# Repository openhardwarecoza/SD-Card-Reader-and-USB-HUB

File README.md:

# SD-Card-Reader-and-USB-HUB
Single PCB for FE1.1 USB Hub and GL827 SD Card Readers x4

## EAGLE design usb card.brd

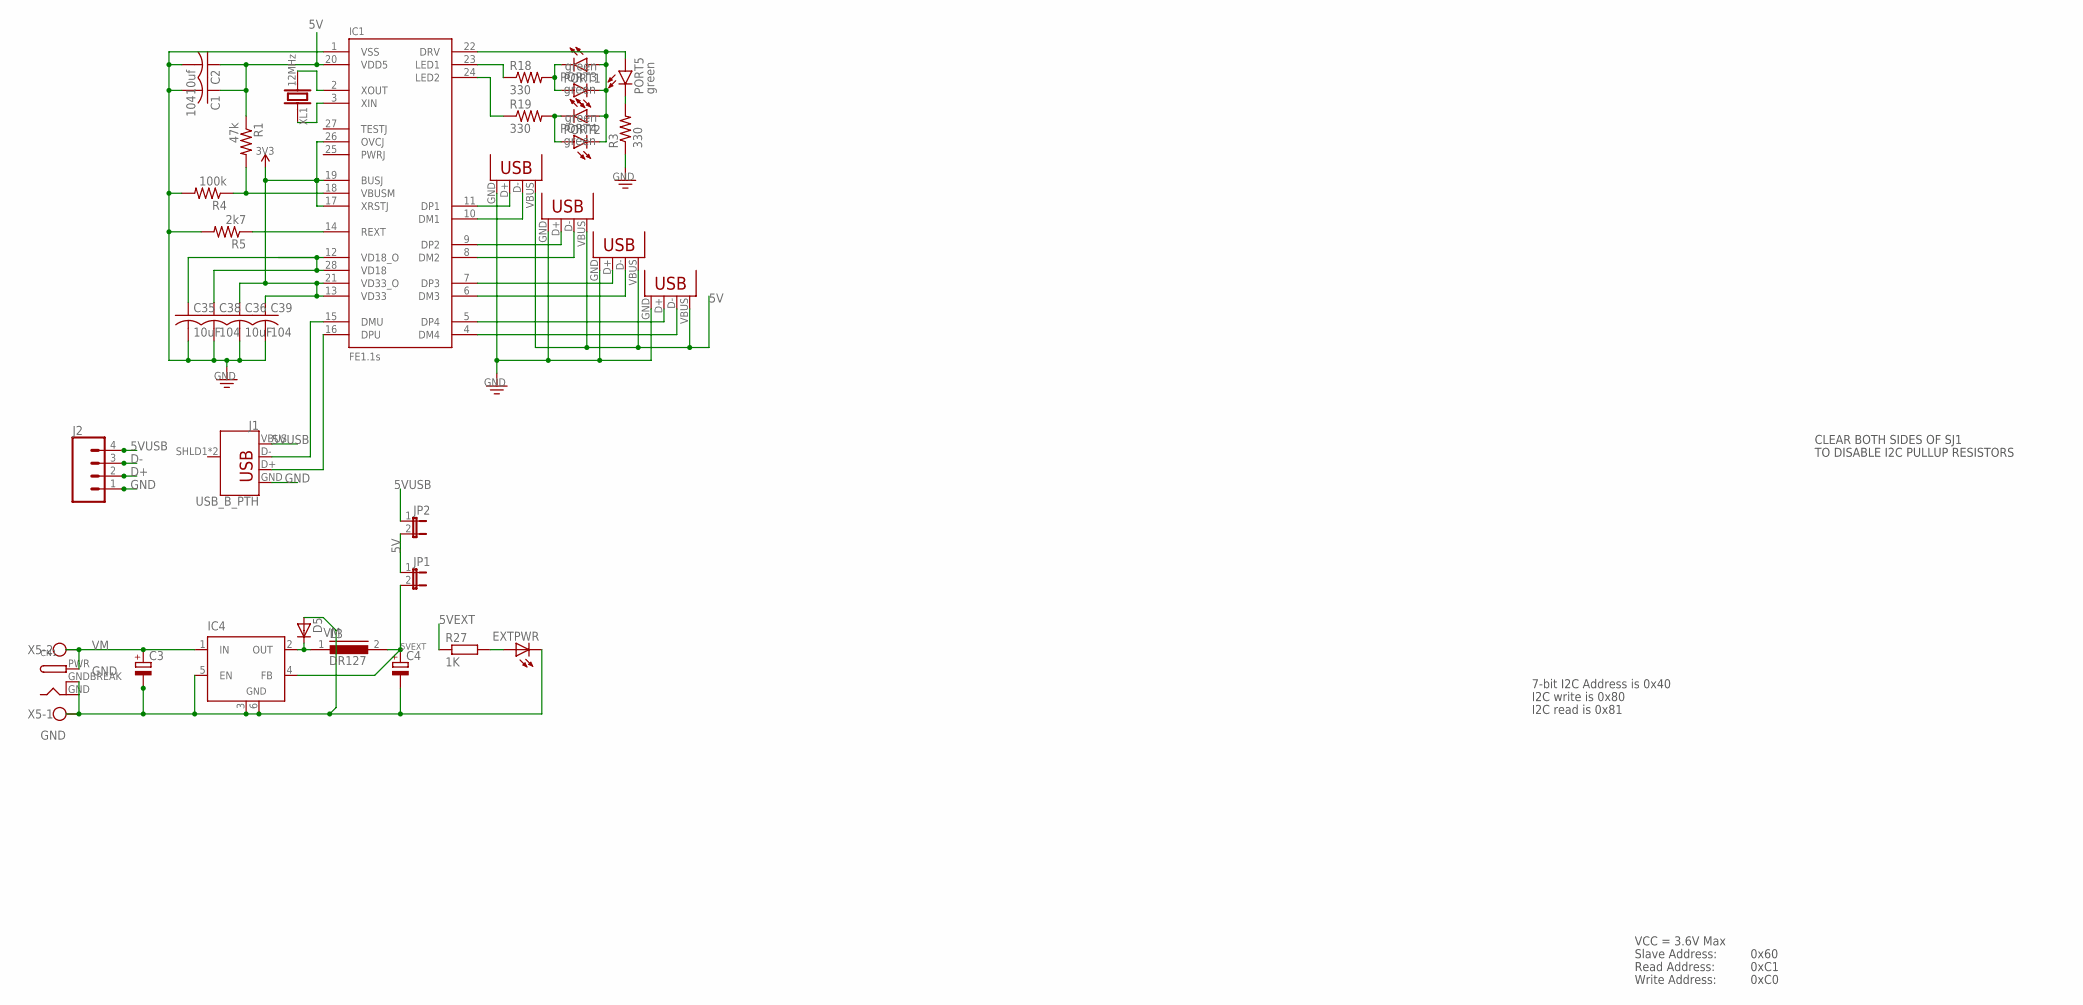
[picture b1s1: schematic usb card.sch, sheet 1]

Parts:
C1, C38, C39: 104; C1206
C2: 10uf; C1206
C3, C4: CPOL-EUE3.5-8; E3,5-8
C35, C36: 10uF; C1206
CN1: DCBARRELPTH; DCJACK_2MM_PTH
D5: D-SOD-80; SOD80
EXTPWR: LEDCHIPLED_1206; CHIPLED_1206
IC1: FE1.1S; FE1.1S_SSOP-28
IC4: LM2596S; TO263-5
J1: USB_B_PTH; USB-B-PTH
J2: CONN_04; 1X04
JP1, JP2: JP1E; JP1
L3: DR127
PORT1, PORT2, PORT3, PORT4, PORT5: green; LED-1206
R1: 47k; R1206
R3, R18, R19: 330; R1206
R4: 100k; R1206
R5: 2k7; R1206
R27: 1K; M1206
USB2, USB3, USB4, USB5: USBA-PTH; USB-A-F-PTH
X5: W237-102
XL1: 12MHz; HC49S

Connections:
3V3: C36.1, C39.1, IC1.13 (VD33), IC1.17 (XRSTJ), IC1.19 (BUSJ), IC1.21 (VD33_O), IC1.26 (OVCJ)
5V: C1.1, C2.1, IC1.20 (VDD5), JP1.1, JP2.2, R1.1, USB2.VBUS, USB3.VBUS, USB4.VBUS, USB5.VBUS; also elsewhere on the board
5VEXT: C4.+, IC4.4 (FB), JP1.2, L3.2, R27.1
5VUSB: J1.VBUS, J2.4, JP2.1
D+: IC1.16 (DPU), J1.D+, J2.2
D-: IC1.15 (DMU), J1.D-, J2.3
DM1: IC1.10 (DM1), USB5.D-; also elsewhere on the board
DM2: IC1.8 (DM2), USB4.D-; also elsewhere on the board
DM3: IC1.6 (DM3), USB3.D-; also elsewhere on the board
DM4: IC1.4 (DM4), USB2.D-; also elsewhere on the board
DP1: IC1.11 (DP1), USB5.D+; also elsewhere on the board
DP2: IC1.9 (DP2), USB4.D+; also elsewhere on the board
DP3: IC1.7 (DP3), USB3.D+; also elsewhere on the board
DP4: IC1.5 (DP4), USB2.D+; also elsewhere on the board
GND: C1.2, C2.2, C3.-, C4.-, C35.2, C36.2, C38.2, C39.2, CN1.GND, CN1.GNDBREAK, D5.2 (A), EXTPWR.C, IC1.1 (VSS), IC4.3 (GND), IC4.5 (EN), IC4.6 (GND), J1.GND, J2.1, R3.1, R4.2, R5.2, USB2.GND, USB3.GND, USB4.GND, USB5.GND, X5.1; also elsewhere on the board
unnamed: IC1.14 (REXT), R5.1
unnamed: PORT2.C, PORT4.A, R19.2
unnamed: IC1.2 (XOUT), XL1.2
unnamed: C35.1, C38.1, IC1.12 (VD18_O), IC1.28 (VD18)
unnamed: IC1.3 (XIN), XL1.1
unnamed: IC1.18 (VBUSM), R1.2, R4.1
unnamed: PORT1.C, PORT3.A, R18.2
unnamed: PORT5.C, R3.2
unnamed: IC1.23 (LED1), R18.1
unnamed: IC1.24 (LED2), R19.1
unnamed: IC1.22 (DRV), PORT1.A, PORT2.A, PORT3.C, PORT4.C, PORT5.A
unnamed: D5.1 (C), IC4.2 (OUT), L3.1
unnamed: EXTPWR.A, R27.2
VM: C3.+, CN1.PWR, IC4.1 (IN), X5.2

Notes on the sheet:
CLEAR BOTH SIDES OF SJ1
TO DISABLE I2C PULLUP RESISTORS
7-bit I2C Address is 0x40
I2C write is 0x80
I2C read is 0x81
VCC = 3.6V Max
Read Address:
Write Address:
Slave Address:
0x60
0xC1
0xC0

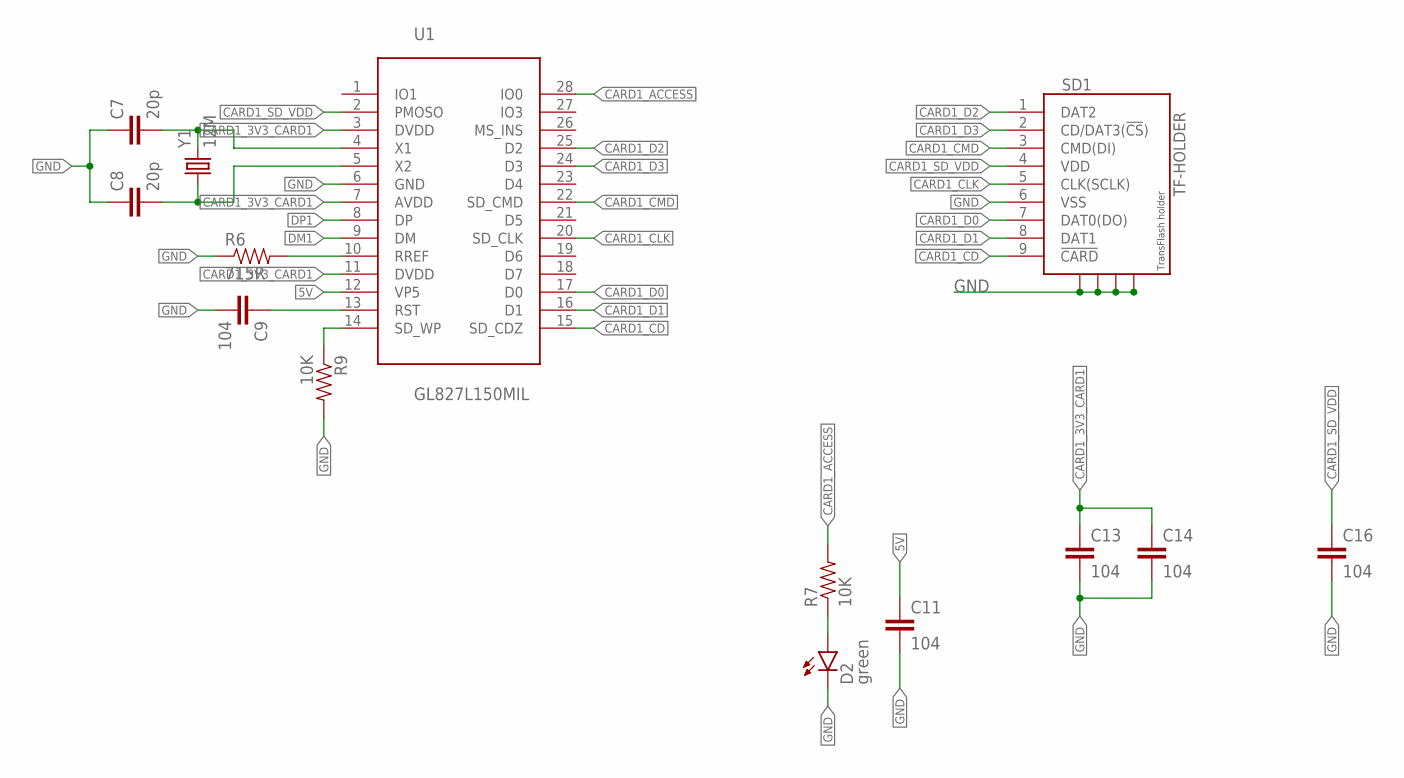
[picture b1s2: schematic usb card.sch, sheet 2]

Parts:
C7, C8: 20p; 1206
C9, C11, C13, C14, C16: 104; 1206
D2: green; LED-1206
R6: 715R; 1206
R7, R9: 10K; 1206
SD1: TF-HOLDER; TF-PULL
U1: GL827L150MIL; SSOP28-39
Y1: 12M; HC49US

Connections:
5V: C11.1, U1.12 (VP5); also elsewhere on the board
CARD1_3V3_CARD1: C13.1, C14.1, U1.3 (DVDD), U1.7 (AVDD), U1.11 (DVDD)
CARD1_ACCESS: R7.2, U1.28 (IO0)
CARD1_CD: SD1.9 (!CARD), U1.15 (SD_CDZ)
CARD1_CLK: SD1.5 (CLK(SCLK)), U1.20 (SD_CLK)
CARD1_CMD: SD1.3 (CMD(DI)), U1.22 (SD_CMD)
CARD1_D0: SD1.7 (DAT0(DO)), U1.17 (D0)
CARD1_D1: SD1.8 (DAT1), U1.16 (D1)
CARD1_D2: SD1.1 (DAT2), U1.25 (D2)
CARD1_D3: SD1.2 (CD/DAT3(!CS!)), U1.24 (D3)
CARD1_SD_VDD: C16.1, SD1.4 (VDD), U1.2 (PMOSO)
DM1: U1.9 (DM); also elsewhere on the board
DP1: U1.8 (DP); also elsewhere on the board
GND: C7.1, C8.1, C9.2, C11.2, C13.2, C14.2, C16.2, D2.C, R6.1, R9.2, SD1.6 (VSS), SD1.S1, SD1.S2, SD1.S3, SD1.S4, U1.6 (GND); also elsewhere on the board
unnamed: C7.2, U1.4 (X1), Y1.2
unnamed: C8.2, U1.5 (X2), Y1.1
unnamed: R6.2, U1.10 (RREF)
unnamed: C9.1, U1.13 (RST)
unnamed: D2.A, R7.1
unnamed: R9.1, U1.14 (SD_WP)

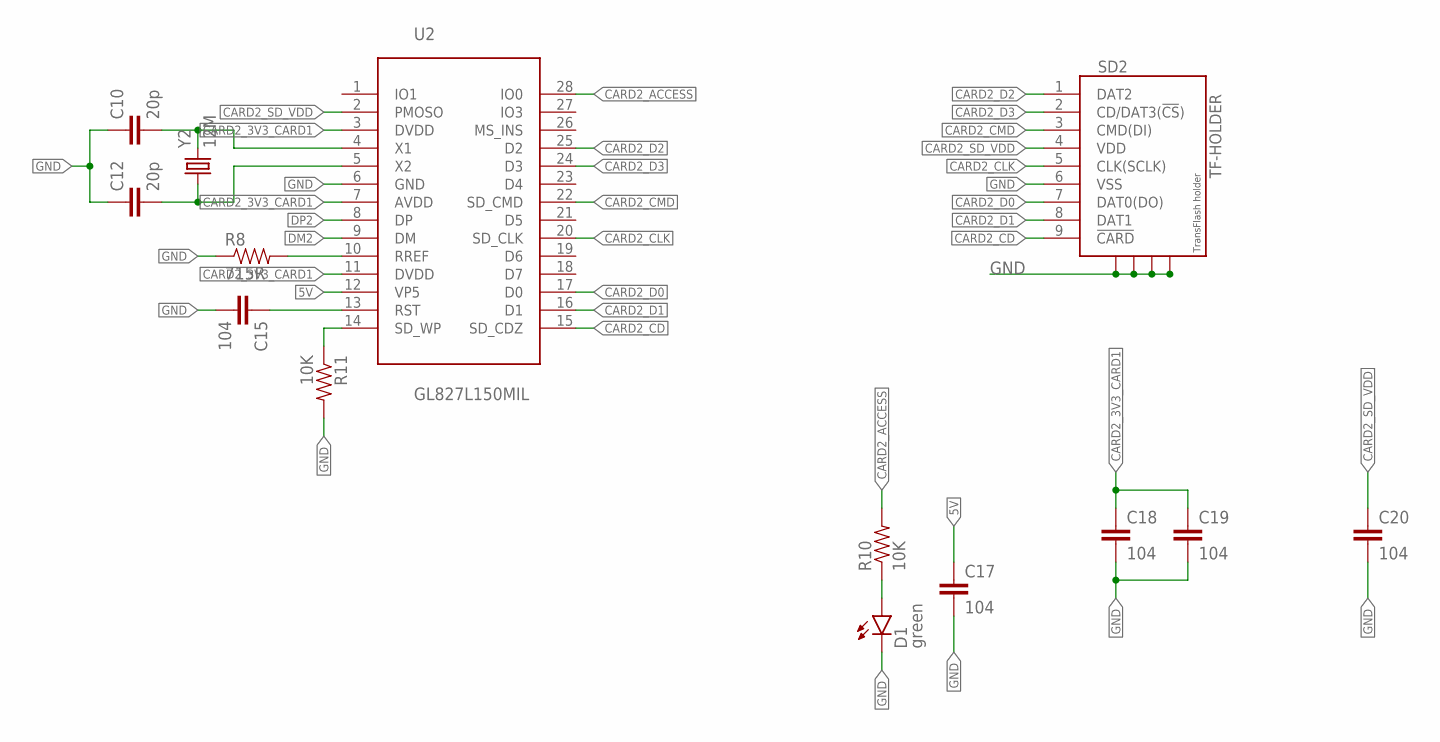
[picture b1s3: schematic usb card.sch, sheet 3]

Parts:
C10, C12: 20p; 1206
C15, C17, C18, C19, C20: 104; 1206
D1: green; LED-1206
R8: 715R; 1206
R10, R11: 10K; 1206
SD2: TF-HOLDER; TF-PULL
U2: GL827L150MIL; SSOP28-39
Y2: 12M; HC49US

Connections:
5V: C17.1, U2.12 (VP5); also elsewhere on the board
CARD2_3V3_CARD1: C18.1, C19.1, U2.3 (DVDD), U2.7 (AVDD), U2.11 (DVDD)
CARD2_ACCESS: R10.2, U2.28 (IO0)
CARD2_CD: SD2.9 (!CARD), U2.15 (SD_CDZ)
CARD2_CLK: SD2.5 (CLK(SCLK)), U2.20 (SD_CLK)
CARD2_CMD: SD2.3 (CMD(DI)), U2.22 (SD_CMD)
CARD2_D0: SD2.7 (DAT0(DO)), U2.17 (D0)
CARD2_D1: SD2.8 (DAT1), U2.16 (D1)
CARD2_D2: SD2.1 (DAT2), U2.25 (D2)
CARD2_D3: SD2.2 (CD/DAT3(!CS!)), U2.24 (D3)
CARD2_SD_VDD: C20.1, SD2.4 (VDD), U2.2 (PMOSO)
DM2: U2.9 (DM); also elsewhere on the board
DP2: U2.8 (DP); also elsewhere on the board
GND: C10.1, C12.1, C15.2, C17.2, C18.2, C19.2, C20.2, D1.C, R8.1, R11.2, SD2.6 (VSS), SD2.S1, SD2.S2, SD2.S3, SD2.S4, U2.6 (GND); also elsewhere on the board
unnamed: C10.2, U2.4 (X1), Y2.2
unnamed: C12.2, U2.5 (X2), Y2.1
unnamed: R8.2, U2.10 (RREF)
unnamed: C15.1, U2.13 (RST)
unnamed: D1.A, R10.1
unnamed: R11.1, U2.14 (SD_WP)

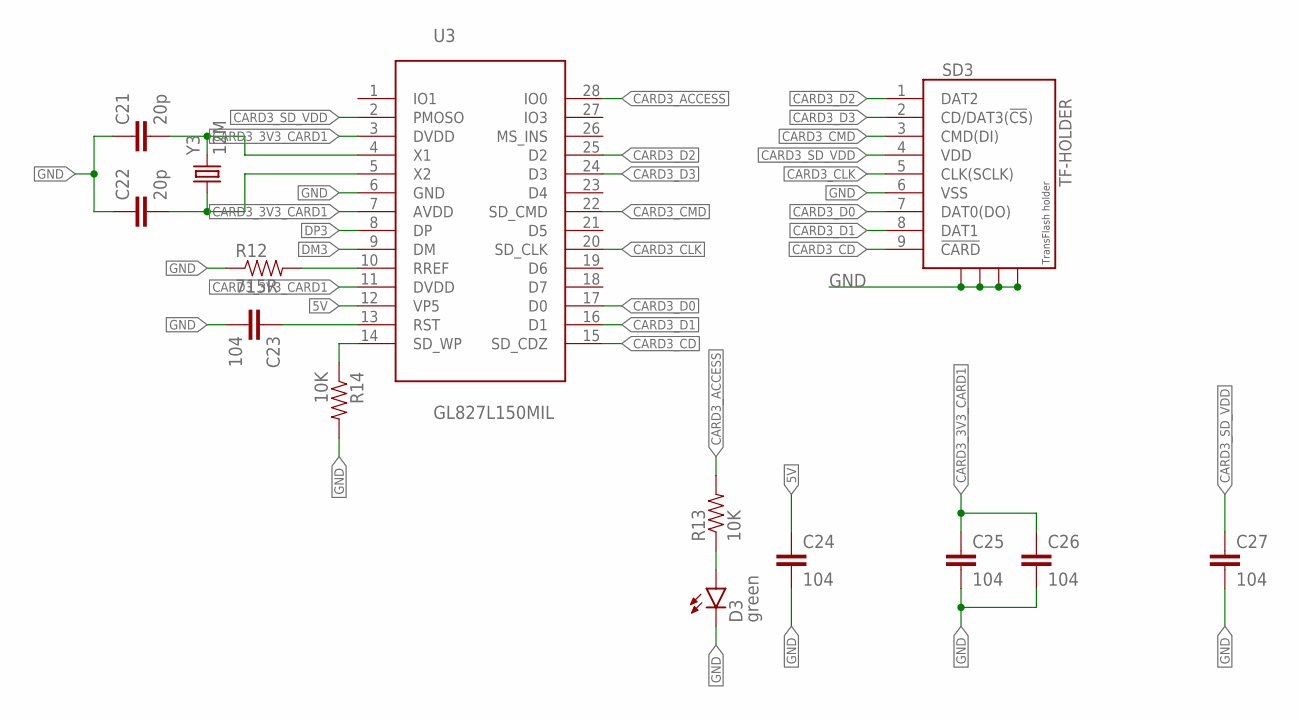
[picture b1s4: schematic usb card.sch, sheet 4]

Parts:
C21, C22: 20p; 1206
C23, C24, C25, C26, C27: 104; 1206
D3: green; LED-1206
R12: 715R; 1206
R13, R14: 10K; 1206
SD3: TF-HOLDER; TF-PULL
U3: GL827L150MIL; SSOP28-39
Y3: 12M; HC49US

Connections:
5V: C24.1, U3.12 (VP5); also elsewhere on the board
CARD3_3V3_CARD1: C25.1, C26.1, U3.3 (DVDD), U3.7 (AVDD), U3.11 (DVDD)
CARD3_ACCESS: R13.2, U3.28 (IO0)
CARD3_CD: SD3.9 (!CARD), U3.15 (SD_CDZ)
CARD3_CLK: SD3.5 (CLK(SCLK)), U3.20 (SD_CLK)
CARD3_CMD: SD3.3 (CMD(DI)), U3.22 (SD_CMD)
CARD3_D0: SD3.7 (DAT0(DO)), U3.17 (D0)
CARD3_D1: SD3.8 (DAT1), U3.16 (D1)
CARD3_D2: SD3.1 (DAT2), U3.25 (D2)
CARD3_D3: SD3.2 (CD/DAT3(!CS!)), U3.24 (D3)
CARD3_SD_VDD: C27.1, SD3.4 (VDD), U3.2 (PMOSO)
DM3: U3.9 (DM); also elsewhere on the board
DP3: U3.8 (DP); also elsewhere on the board
GND: C21.1, C22.1, C23.2, C24.2, C25.2, C26.2, C27.2, D3.C, R12.1, R14.2, SD3.6 (VSS), SD3.S1, SD3.S2, SD3.S3, SD3.S4, U3.6 (GND); also elsewhere on the board
unnamed: C21.2, U3.4 (X1), Y3.2
unnamed: C22.2, U3.5 (X2), Y3.1
unnamed: R12.2, U3.10 (RREF)
unnamed: C23.1, U3.13 (RST)
unnamed: D3.A, R13.1
unnamed: R14.1, U3.14 (SD_WP)

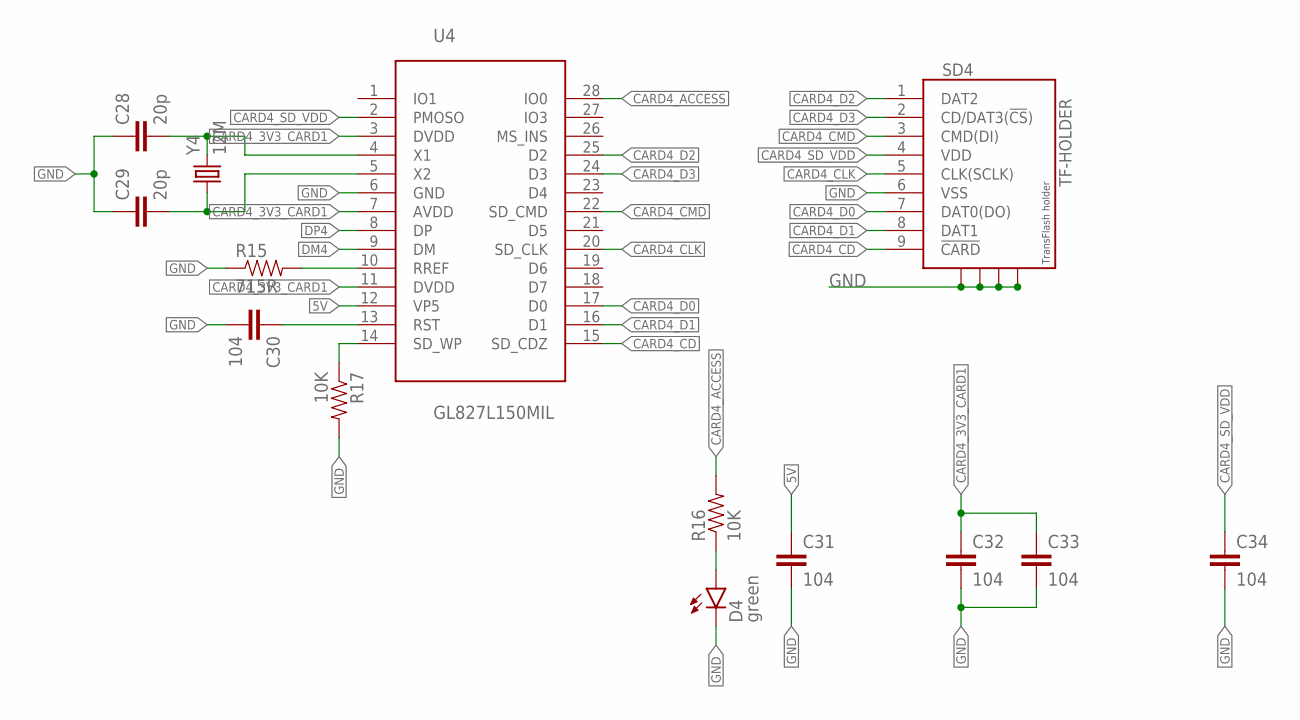
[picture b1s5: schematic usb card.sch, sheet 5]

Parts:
C28, C29: 20p; 1206
C30, C31, C32, C33, C34: 104; 1206
D4: green; LED-1206
R15: 715R; 1206
R16, R17: 10K; 1206
SD4: TF-HOLDER; TF-PULL
U4: GL827L150MIL; SSOP28-39
Y4: 12M; HC49US

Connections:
5V: C31.1, U4.12 (VP5); also elsewhere on the board
CARD4_3V3_CARD1: C32.1, C33.1, U4.3 (DVDD), U4.7 (AVDD), U4.11 (DVDD)
CARD4_ACCESS: R16.2, U4.28 (IO0)
CARD4_CD: SD4.9 (!CARD), U4.15 (SD_CDZ)
CARD4_CLK: SD4.5 (CLK(SCLK)), U4.20 (SD_CLK)
CARD4_CMD: SD4.3 (CMD(DI)), U4.22 (SD_CMD)
CARD4_D0: SD4.7 (DAT0(DO)), U4.17 (D0)
CARD4_D1: SD4.8 (DAT1), U4.16 (D1)
CARD4_D2: SD4.1 (DAT2), U4.25 (D2)
CARD4_D3: SD4.2 (CD/DAT3(!CS!)), U4.24 (D3)
CARD4_SD_VDD: C34.1, SD4.4 (VDD), U4.2 (PMOSO)
DM4: U4.9 (DM); also elsewhere on the board
DP4: U4.8 (DP); also elsewhere on the board
GND: C28.1, C29.1, C30.2, C31.2, C32.2, C33.2, C34.2, D4.C, R15.1, R17.2, SD4.6 (VSS), SD4.S1, SD4.S2, SD4.S3, SD4.S4, U4.6 (GND); also elsewhere on the board
unnamed: C28.2, U4.4 (X1), Y4.2
unnamed: C29.2, U4.5 (X2), Y4.1
unnamed: R15.2, U4.10 (RREF)
unnamed: C30.1, U4.13 (RST)
unnamed: D4.A, R16.1
unnamed: R17.1, U4.14 (SD_WP)

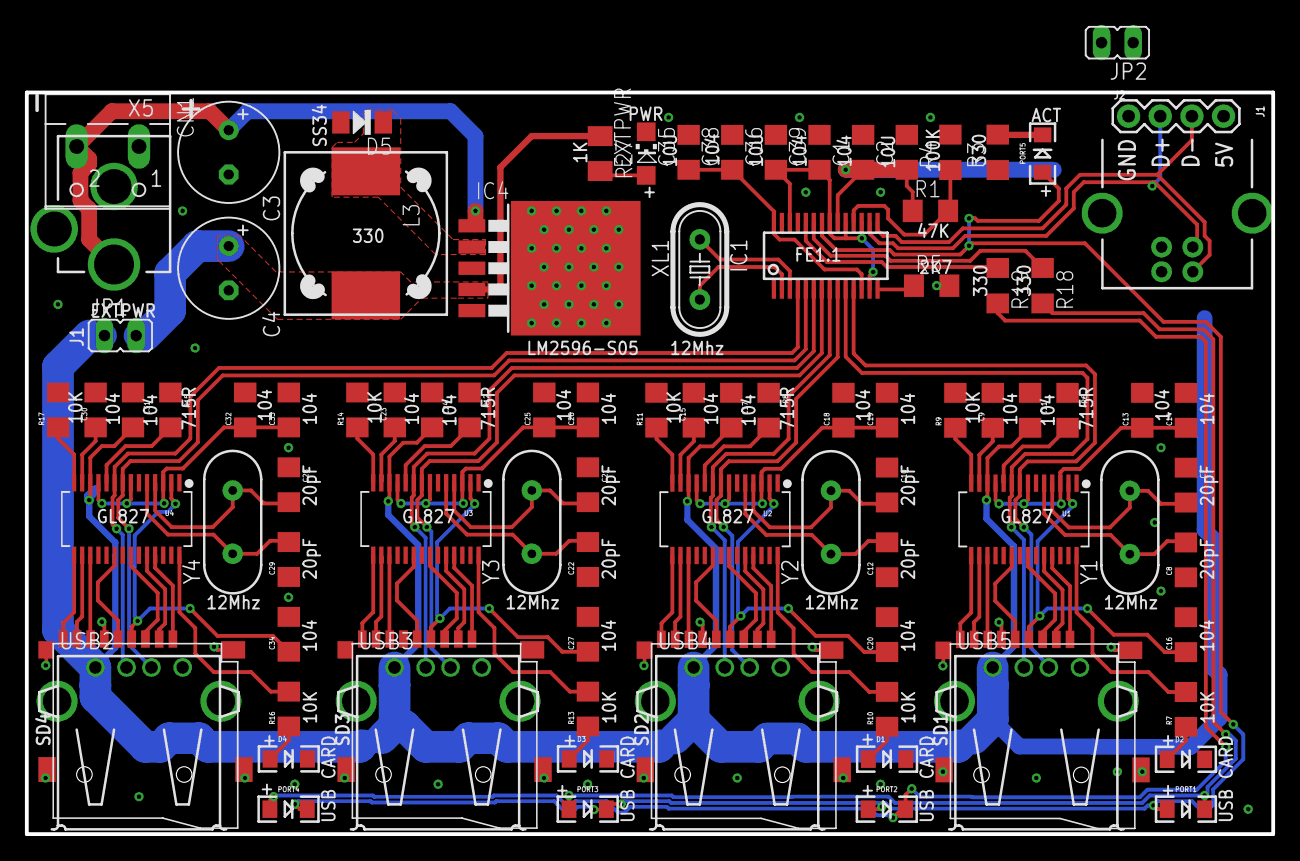
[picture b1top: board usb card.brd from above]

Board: 2 copper layers, 100.0 x 59.5 mm, 92 parts (0 on the bottom side), 93 nets.

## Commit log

2018-10-23 archive

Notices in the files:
parts and their libraries:
SparkFun-Connectors: Licensing: Creative Commons ShareAlike 4.0 International - https://creativecommons.org/licenses/by-sa/4.0
